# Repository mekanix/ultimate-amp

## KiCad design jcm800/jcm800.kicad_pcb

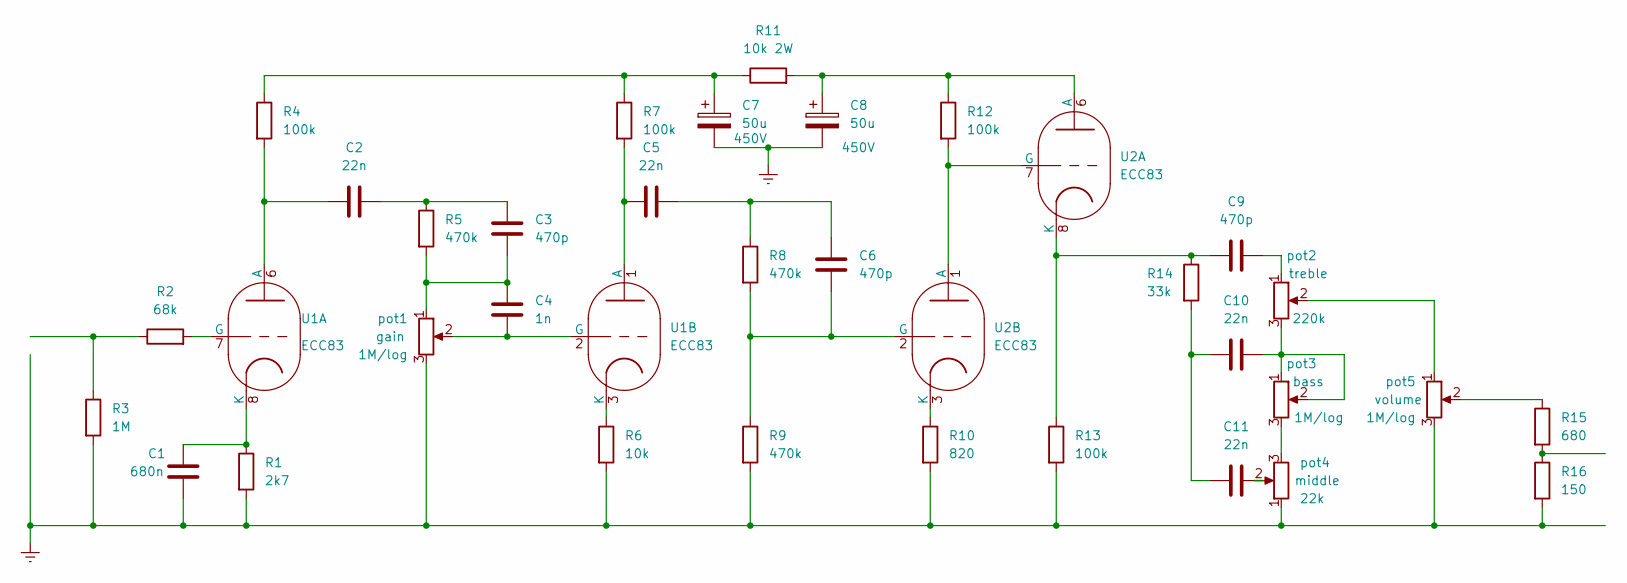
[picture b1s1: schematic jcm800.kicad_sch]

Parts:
C1: 680n; CP_Axial_L10.0mm_D4.5mm_P15.00mm_Horizontal
C2, C5, C10, C11: 22n; CP_Axial_L10.0mm_D4.5mm_P15.00mm_Horizontal
C3, C6, C9: 470p; CP_Axial_L10.0mm_D4.5mm_P15.00mm_Horizontal
C4: 1n; CP_Axial_L10.0mm_D4.5mm_P15.00mm_Horizontal
C7, C8: 50u; CP_Axial_L10.0mm_D4.5mm_P15.00mm_Horizontal
R1: 2k7; R_Axial_DIN0207_L6.3mm_D2.5mm_P2.54mm_Vertical
R2: 68k; R_Axial_DIN0207_L6.3mm_D2.5mm_P2.54mm_Vertical
R3: 1M; R_Axial_DIN0207_L6.3mm_D2.5mm_P2.54mm_Vertical
R4, R7, R12, R13: 100k; R_Axial_DIN0207_L6.3mm_D2.5mm_P2.54mm_Vertical
R5, R8, R9: 470k; R_Axial_DIN0207_L6.3mm_D2.5mm_P2.54mm_Vertical
R6: 10k; R_Axial_DIN0207_L6.3mm_D2.5mm_P2.54mm_Vertical
R10: 820; R_Axial_DIN0207_L6.3mm_D2.5mm_P2.54mm_Vertical
R11: 10k 2W; R_Axial_DIN0207_L6.3mm_D2.5mm_P2.54mm_Vertical
R14: 33k; R_Axial_DIN0207_L6.3mm_D2.5mm_P2.54mm_Vertical
R15: 680; R_Axial_DIN0207_L6.3mm_D2.5mm_P2.54mm_Vertical
R16: 150; R_Axial_DIN0207_L6.3mm_D2.5mm_P2.54mm_Vertical
U1, U2: ECC83; Valve_Noval_P
pot1, pot3, pot5: 1M/log; Potentiometer_ACP_CA6-H2,5_Horizontal
pot2: 220k; Potentiometer_ACP_CA6-H2,5_Horizontal
pot4: 22k; Potentiometer_ACP_CA6-H2,5_Horizontal

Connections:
Earth: C1.2, C7.2, C8.2, R1.2, R3.2, R6.2, R9.2, R10.2, R13.2, R16.2, pot1.3, pot4.1, pot5.3
unnamed: C2.2, C3.1, R5.1
unnamed: C3.2, C4.1, R5.2, pot1.1
unnamed: C5.2, C6.1, R8.1
unnamed: C7.1, R4.1, R7.1, R11.1
unnamed: C9.2, pot2.1
unnamed: C10.1, C11.1, R14.2
unnamed: C10.2, pot2.3, pot3.1, pot3.2
unnamed: C11.2, pot4.2
unnamed: R2.1, R3.1
unnamed: R15.1, pot5.2
unnamed: R15.2, R16.1
unnamed: C2.1, R4.2, U1.6 (A)
unnamed: R2.2, U1.7 (G)
unnamed: C1.1, R1.1, U1.8 (K)
unnamed: C5.1, R7.2, U1.1 (A)
unnamed: C4.2, U1.2 (G), pot1.2
unnamed: R6.1, U1.3 (K)
unnamed: C8.1, R11.2, R12.1, U2.6 (A)
unnamed: R12.2, U2.1 (A), U2.7 (G)
unnamed: C9.1, R13.1, R14.1, U2.8 (K)
unnamed: C6.2, R8.2, R9.1, U2.2 (G)
unnamed: R10.1, U2.3 (K)
unnamed: pot2.2, pot5.1
unnamed: pot3.3, pot4.3

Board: 2 copper layers, 34 parts (0 on the bottom side), 25 nets, no tracks yet.
